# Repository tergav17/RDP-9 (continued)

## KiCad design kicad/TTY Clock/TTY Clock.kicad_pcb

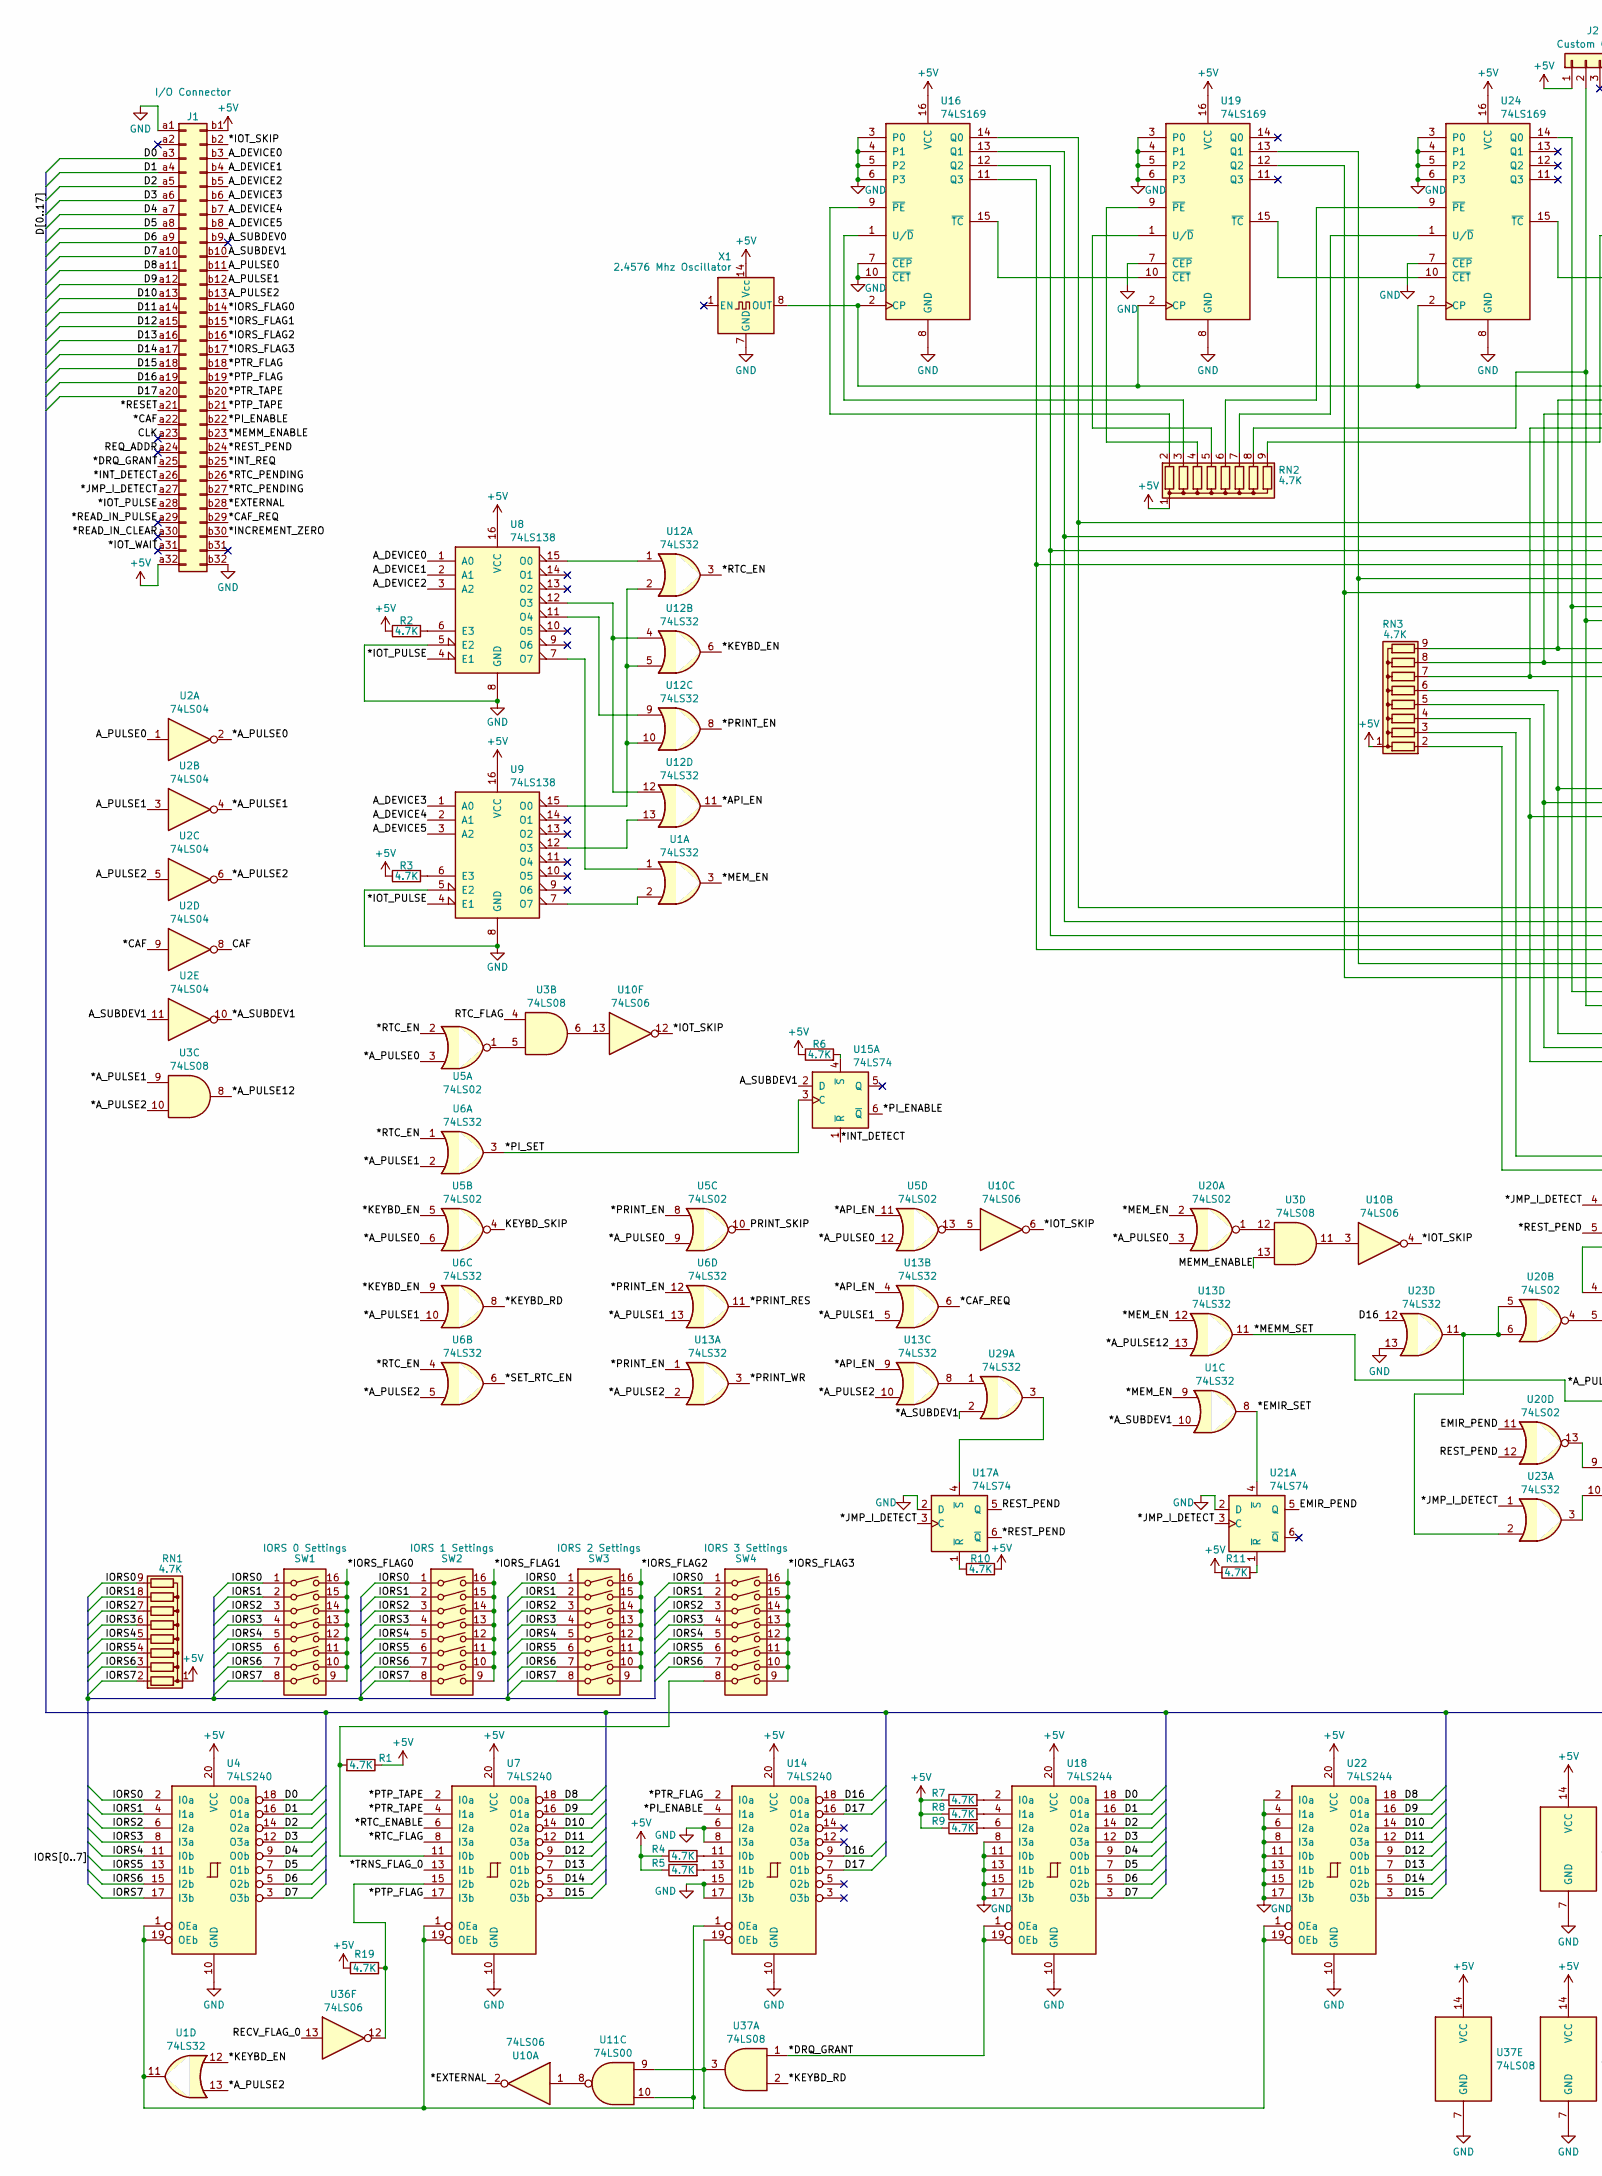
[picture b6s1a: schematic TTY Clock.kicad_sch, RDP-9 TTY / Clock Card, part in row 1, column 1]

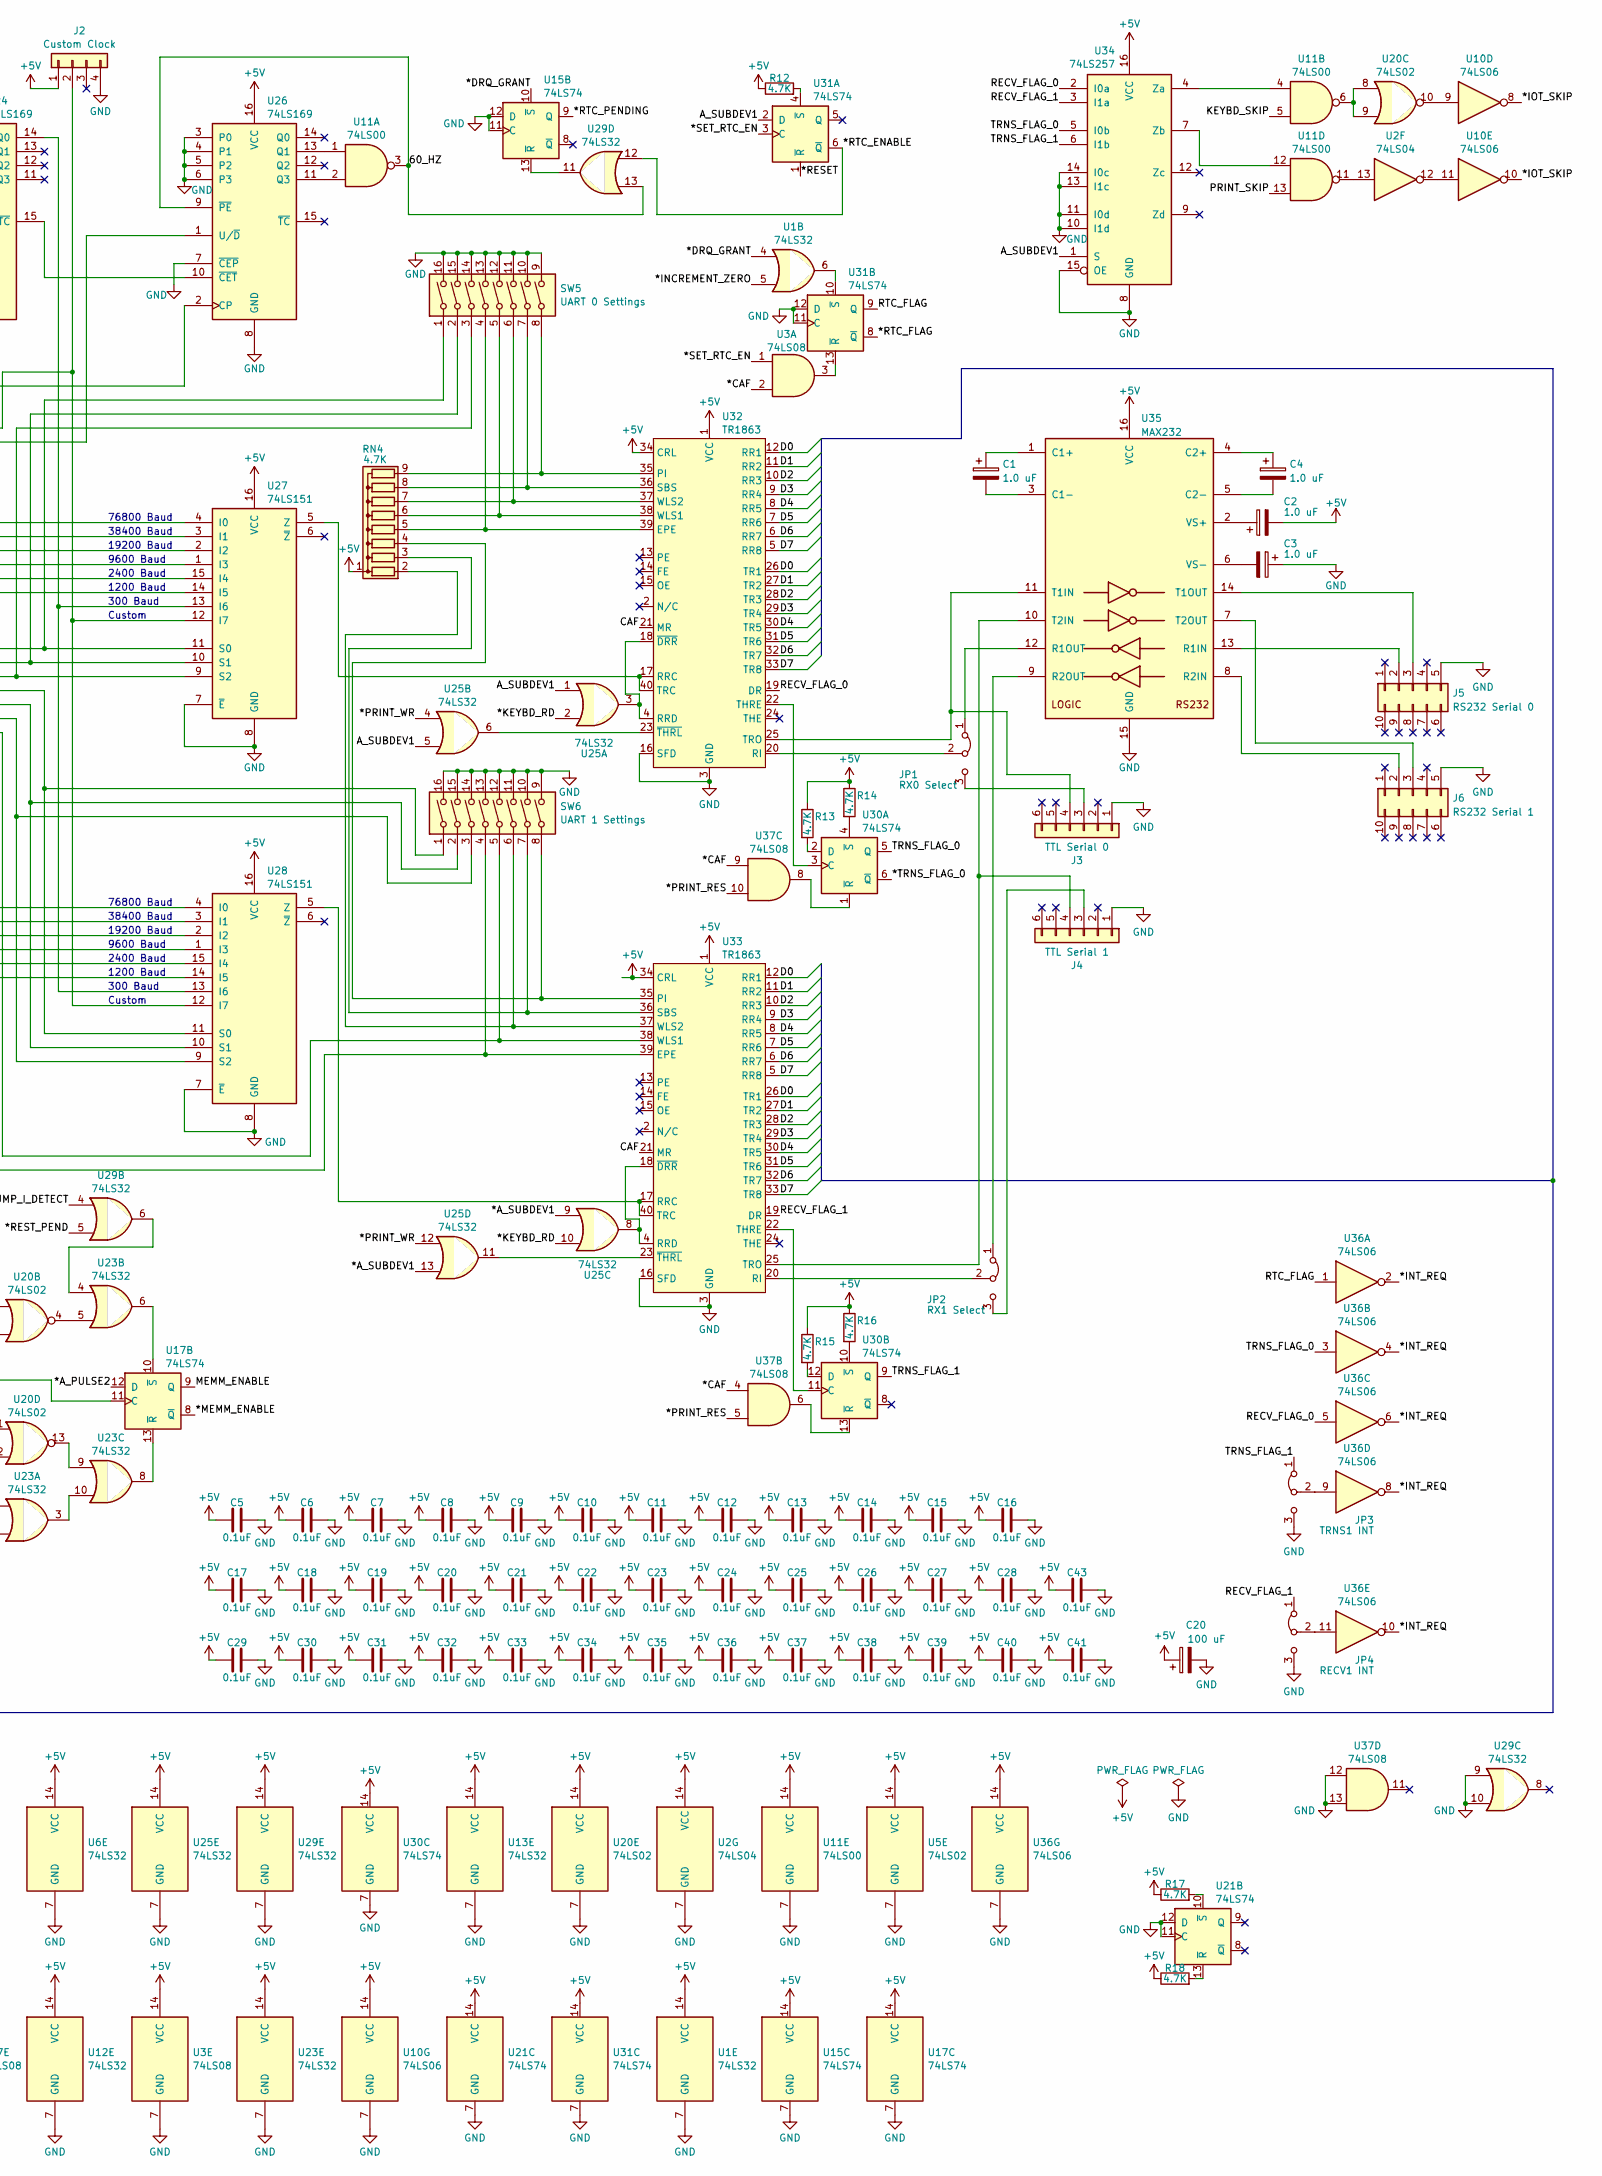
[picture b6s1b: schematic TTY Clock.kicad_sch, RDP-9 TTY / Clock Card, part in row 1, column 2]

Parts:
C1, C2, C3, C4: 1.0 uF; CP_Radial_D5.0mm_P2.00mm
C5, C6, C7, C8, C9, C10, C11, C12, C13, C14, C15, C16, C17, C18, C19, C21, C22, C23, C24, C25, C26, C27, C28, C29, C30, C31, C32, C33, C34, C35, C36, C37, C38, C39, C40, C41, C43: 0.1uF; C_Disc_D5.0mm_W2.5mm_P5.00mm
C20: 100 uF; CP_Radial_D6.3mm_P2.50mm
J1: I/O Connector; DIN41612_B_2x32_Male_Horizontal_THT
J2: Custom Clock; PinHeader_1x04_P2.54mm_Horizontal
J3: TTL Serial 0; PinHeader_1x06_P2.54mm_Horizontal
J4: TTL Serial 1; PinHeader_1x06_P2.54mm_Horizontal
J5: RS232 Serial 0; IDC-Header_2x05_P2.54mm_Horizontal
J6: RS232 Serial 1; IDC-Header_2x05_P2.54mm_Horizontal
JP1: RX0 Select; PinHeader_1x03_P2.54mm_Vertical
JP2: RX1 Select; PinHeader_1x03_P2.54mm_Vertical
JP3: TRNS1 INT; PinHeader_1x03_P2.54mm_Vertical
JP4: RECV1 INT; PinHeader_1x03_P2.54mm_Vertical
R1, R2, R3, R4, R5, R6, R7, R8, R9, R10, R11, R12, R13, R14, R15, R16, R17, R18, R19: 4.7K; R_Axial_DIN0207_L6.3mm_D2.5mm_P7.62mm_Horizontal
RN1, RN2, RN3, RN4: 4.7K; R_Array_SIP9
SW1: IORS 0 Settings; SW_DIP_SPSTx08_Slide_9.78x22.5mm_W7.62mm_P2.54mm
SW2: IORS 1 Settings; SW_DIP_SPSTx08_Slide_9.78x22.5mm_W7.62mm_P2.54mm
SW3: IORS 2 Settings; SW_DIP_SPSTx08_Slide_9.78x22.5mm_W7.62mm_P2.54mm
SW4: IORS 3 Settings; SW_DIP_SPSTx08_Slide_9.78x22.5mm_W7.62mm_P2.54mm
SW5: UART 0 Settings; SW_DIP_SPSTx08_Slide_9.78x22.5mm_W7.62mm_P2.54mm
SW6: UART 1 Settings; SW_DIP_SPSTx08_Slide_9.78x22.5mm_W7.62mm_P2.54mm
U1, U6, U12, U13, U23, U25, U29: 74LS32; DIP-14_W7.62mm
U2: 74LS04; DIP-14_W7.62mm
U3, U37: 74LS08; DIP-14_W7.62mm
U4, U7, U14: 74LS240; DIP-20_W7.62mm
U5, U20: 74LS02; DIP-14_W7.62mm
U8, U9: 74LS138; DIP-16_W7.62mm
U10, U36: 74LS06; DIP-14_W7.62mm
U11: 74LS00; DIP-14_W7.62mm
U15, U17, U21, U30, U31: 74LS74; DIP-14_W7.62mm
U16, U19, U24, U26: 74LS169; DIP-16_W7.62mm
U18, U22: 74LS244; DIP-20_W7.62mm
U27, U28: 74LS151; DIP-16_W7.62mm
U32, U33: TR1863; DIP-40_W15.24mm
U34: 74LS257; DIP-16_W7.62mm
U35: MAX232; DIP-16_W7.62mm
X1: 2.4576 Mhz Oscillator; Oscillator_DIP-14

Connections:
+5V: C2.2, C5.1, C6.1, C7.1, C8.1, C9.1, C10.1, C11.1, C12.1, C13.1, C14.1, C15.1, C16.1, C17.1, C18.1, C19.1, C20.1, C21.1, C22.1, C23.1, C24.1, C25.1, C26.1, C27.1, C28.1, C29.1, C30.1, C31.1, C32.1, C33.1, C34.1, C35.1, C36.1, C37.1, C38.1, C39.1, C40.1, C41.1, C43.1, J1.a32, J1.b1, J2.1, R1.1, R2.1, R3.1, R4.1, R5.1, R6.1, R7.1, R8.1, R9.1, R10.2, R11.1, R12.1, R13.1, R14.1, R15.1, R16.1, R17.1, R18.1, R19.1, RN1.1 (common), RN2.1 (common), RN3.1 (common), RN4.1 (common), U1.14 (VCC), U2.14 (VCC), U3.14 (VCC), U4.20 (VCC), U5.14 (VCC), U6.14 (VCC), U7.20 (VCC), U8.16 (VCC), U9.16 (VCC), U10.14 (VCC), U11.14 (VCC), U12.14 (VCC), U13.14 (VCC), U14.20 (VCC), U15.14 (VCC), U16.16 (VCC), U17.14 (VCC), U18.20 (VCC), U19.16 (VCC), U20.14 (VCC), U21.14 (VCC), U22.20 (VCC), U23.14 (VCC), U24.16 (VCC), U25.14 (VCC), U26.16 (VCC), U27.16 (VCC), U28.16 (VCC), U29.14 (VCC), U30.14 (VCC), U31.14 (VCC), U32.1 (VCC), U32.34 (CRL), U33.1 (VCC), U33.34 (CRL), U34.16 (VCC), U35.16 (VCC), U36.14 (VCC), U37.14 (VCC), X1.14 (Vcc); also elsewhere on the board
/60_HZ: U11.3, U26.9 (~PE), U29.13
/*API_EN: U5.11, U12.11, U13.4, U13.9
/*A_PULSE0: U2.2, U5.3, U5.6, U5.9, U5.12, U20.3
/*A_PULSE1: U2.4, U3.9, U6.2, U6.10, U6.13, U13.5
/*A_PULSE2: U1.13, U2.6, U3.10, U6.5, U13.2, U13.10, U17.12 (D)
/*A_PULSE12: U3.8, U13.13
/*A_SUBDEV1: U1.10, U2.10, U25.9, U25.13, U29.2
/*CAF: J1.a22, U2.9, U3.2, U37.4, U37.9
/*CAF_REQ: J1.b29, U13.6
/*DRQ_GRANT: J1.a25, U1.4, U15.10 (~S), U18.1 (OEa), U18.19 (OEb), U37.1
/*EMIR_SET: U1.8, U21.4 (~S)
/*EXTERNAL: J1.b28, U10.2
/*INCREMENT_ZERO: J1.b30, U1.5
/*INT_DETECT: J1.a26, U15.1 (~R)
/*INT_REQ: J1.b25, U36.2, U36.4, U36.6, U36.8, U36.10
/*IORS_FLAG0: J1.b14, SW1.9, SW1.10, SW1.11, SW1.12, SW1.13, SW1.14, SW1.15, SW1.16
/*IORS_FLAG1: J1.b15, SW2.9, SW2.10, SW2.11, SW2.12, SW2.13, SW2.14, SW2.15, SW2.16
/*IORS_FLAG2: J1.b16, SW3.9, SW3.10, SW3.11, SW3.12, SW3.13, SW3.14, SW3.15, SW3.16
/*IORS_FLAG3: J1.b17, SW4.9, SW4.10, SW4.11, SW4.12, SW4.13, SW4.14, SW4.15, SW4.16
/*IOT_PULSE: J1.a28, U8.4 (E1), U9.4 (E1)
/*IOT_SKIP: J1.b2, U10.4, U10.6, U10.8, U10.10, U10.12
/*IOT_WAIT: J1.a31
/*JMP_I_DETECT: J1.a27, U17.3 (C), U21.3 (C), U23.1, U29.4
/*KEYBD_EN: U1.12, U5.5, U6.9, U12.6
/*KEYBD_RD: U6.8, U25.2, U25.10, U37.2
/*MEMM_ENABLE: J1.b23, U17.8 (~Q)
/*MEMM_SET: U13.11, U17.11 (C)
/*MEM_EN: U1.3, U1.9, U13.12, U20.2
/*PI_ENABLE: J1.b22, U14.4 (I1a), U15.6 (~Q)
/*PI_SET: U6.3, U15.3 (C)
/*PRINT_EN: U5.8, U6.12, U12.8, U13.1
/*PRINT_RES: U6.11, U37.5, U37.10
/*PRINT_WR: U13.3, U25.4, U25.12
/*PTP_FLAG: J1.b19, U7.17 (I3b)
/*PTP_TAPE: J1.b21, U7.2 (I0a)
/*PTR_FLAG: J1.b18, U14.2 (I0a)
/*PTR_TAPE: J1.b20, U7.4 (I1a)
/*READ_IN_CLEAR: J1.a30
/*READ_IN_PULSE: J1.a29
/*RESET: J1.a21, U31.1 (~R)
/*REST_PEND: J1.b24, U17.6 (~Q), U29.5
/*RTC_EN: U5.2, U6.1, U6.4, U12.3
/*RTC_ENABLE: U7.6 (I2a), U29.12, U31.6 (~Q)
/*RTC_FLAG: U7.8 (I3a), U31.8 (~Q)
/*RTC_PENDING: J1.b26, J1.b27, U15.9 (Q)
/*SET_RTC_EN: U3.1, U6.6, U31.3 (C)
/*TRNS_FLAG_0: U7.13 (I1b), U30.6 (~Q)
/A_DEVICE0: J1.b3, U8.1 (A0)
/A_DEVICE1: J1.b4, U8.2 (A1)
/A_DEVICE2: J1.b5, U8.3 (A2)
/A_DEVICE3: J1.b6, U9.1 (A0)
/A_DEVICE4: J1.b7, U9.2 (A1)
/A_DEVICE5: J1.b8, U9.3 (A2)
/A_PULSE0: J1.b11, U2.1
/A_PULSE1: J1.b12, U2.3
/A_PULSE2: J1.b13, U2.5
/A_SUBDEV0: J1.b9
/A_SUBDEV1: J1.b10, U2.11, U15.2 (D), U25.1, U25.5, U31.2 (D), U34.1 (S)
/CAF: U2.8, U32.21 (MR), U33.21 (MR)
/CLK: J1.a23
/D0: J1.a3, U4.18 (O0a), U18.18 (O0a), U32.12 (RR1), U32.26 (TR1), U33.12 (RR1), U33.26 (TR1)
/D1: J1.a4, U4.16 (O1a), U18.16 (O1a), U32.11 (RR2), U32.27 (TR2), U33.11 (RR2), U33.27 (TR2)
/D2: J1.a5, U4.14 (O2a), U18.14 (O2a), U32.10 (RR3), U32.28 (TR3), U33.10 (RR3), U33.28 (TR3)
/D3: J1.a6, U4.12 (O3a), U18.12 (O3a), U32.9 (RR4), U32.29 (TR4), U33.9 (RR4), U33.29 (TR4)
/D4: J1.a7, U4.9 (O0b), U18.9 (O0b), U32.8 (RR5), U32.30 (TR5), U33.8 (RR5), U33.30 (TR5)
/D5: J1.a8, U4.7 (O1b), U18.7 (O1b), U32.7 (RR6), U32.31 (TR6), U33.7 (RR6), U33.31 (TR6)
/D6: J1.a9, U4.5 (O2b), U18.5 (O2b), U32.6 (RR7), U32.32 (TR7), U33.6 (RR7), U33.32 (TR7)
/D7: J1.a10, U4.3 (O3b), U18.3 (O3b), U32.5 (RR8), U32.33 (TR8), U33.5 (RR8), U33.33 (TR8)
/D8: J1.a11, U7.18 (O0a), U22.18 (O0a)
/D9: J1.a12, U7.16 (O1a), U22.16 (O1a)
/D10: J1.a13, U7.14 (O2a), U22.14 (O2a)
/D11: J1.a14, U7.12 (O3a), U22.12 (O3a)
/D12: J1.a15, U7.9 (O0b), U22.9 (O0b)
/D13: J1.a16, U7.7 (O1b), U22.7 (O1b)
/D14: J1.a17, U7.5 (O2b), U22.5 (O2b)
/D15: J1.a18, U7.3 (O3b), U22.3 (O3b)
/D16: J1.a19, U14.9 (O0b), U14.18 (O0a), U23.12
/D17: J1.a20, U14.7 (O1b), U14.16 (O1a)
/EMIR_PEND: U20.11, U21.5 (Q)
/IORS0: RN1.9 (R8), SW1.1, SW2.1, SW3.1, SW4.1, U4.2 (I0a)
/IORS1: RN1.8 (R7), SW1.2, SW2.2, SW3.2, SW4.2, U4.4 (I1a)
/IORS2: RN1.7 (R6), SW1.3, SW2.3, SW3.3, SW4.3, U4.6 (I2a)
/IORS3: RN1.6 (R5), SW1.4, SW2.4, SW3.4, SW4.4, U4.8 (I3a)
/IORS4: RN1.5 (R4), SW1.5, SW2.5, SW3.5, SW4.5, U4.11 (I0b)
/IORS5: RN1.4 (R3), SW1.6, SW2.6, SW3.6, SW4.6, U4.13 (I1b)
/IORS6: RN1.3 (R2), SW1.7, SW2.7, SW3.7, SW4.7, U4.15 (I2b)
/IORS7: RN1.2 (R1), SW1.8, SW2.8, SW3.8, U4.17 (I3b)
/KEYBD_SKIP: U5.4, U11.5
/MEMM_ENABLE: U3.13, U17.9 (Q)
/PRINT_SKIP: U5.10, U11.13
/RECV_FLAG_0: U32.19 (DR), U34.2 (I0a), U36.5, U36.13
/RECV_FLAG_1: JP4.1 (A), U33.19 (DR), U34.3 (I1a)
/REQ_ADDR: J1.a24
/REST_PEND: U17.5 (Q), U20.12
/RTC_FLAG: U3.4, U31.9 (Q), U36.1
/TRNS_FLAG_0: U30.5 (Q), U34.5 (I0b), U36.3
/TRNS_FLAG_1: JP3.1 (A), U30.9 (Q), U34.6 (I1b)
GND: C3.1, C5.2, C6.2, C7.2, C8.2, C9.2, C10.2, C11.2, C12.2, C13.2, C14.2, C15.2, C16.2, C17.2, C18.2, C19.2, C20.2, C21.2, C22.2, C23.2, C24.2, C25.2, C26.2, C27.2, C28.2, C29.2, C30.2, C31.2, C32.2, C33.2, C34.2, C35.2, C36.2, C37.2, C38.2, C39.2, C40.2, C41.2, C43.2, J1.a1, J1.b32, J2.4, J3.1, J4.1, J5.5, J6.5, JP3.3 (B), JP4.3 (B), SW5.9, SW5.10, SW5.11, SW5.12, SW5.13, SW5.14, SW5.15, SW5.16, SW6.9, SW6.10, SW6.11, SW6.12, SW6.13, SW6.14, SW6.15, SW6.16, U1.7 (GND), U2.7 (GND), U3.7 (GND), U4.10 (GND), U5.7 (GND), U6.7 (GND), U7.10 (GND), U8.5 (E2), U8.8 (GND), U9.5 (E2), U9.8 (GND), U10.7 (GND), U11.7 (GND), U12.7 (GND), U13.7 (GND), U14.6 (I2a), U14.8 (I3a), U14.10 (GND), U14.15 (I2b), U14.17 (I3b), U15.7 (GND), U15.11 (C), U15.12 (D), U16.3 (P0), U16.4 (P1), U16.5 (P2), U16.6 (P3), U16.7 (~CEP), U16.8 (GND), U16.10 (~CET), U17.2 (D), U17.7 (GND), U18.8 (I3a), U18.10 (GND), U18.11 (I0b), U18.13 (I1b), U18.15 (I2b), U18.17 (I3b), U19.3 (P0), U19.4 (P1), U19.5 (P2), U19.6 (P3), U19.7 (~CEP), U19.8 (GND), U20.7 (GND), U21.2 (D), U21.7 (GND), U21.11 (C), U21.12 (D), U22.2 (I0a), U22.4 (I1a), U22.6 (I2a), U22.8 (I3a), U22.10 (GND), U22.11 (I0b), U22.13 (I1b), U22.15 (I2b), U22.17 (I3b), U23.7 (GND), U23.13, U24.3 (P0), U24.4 (P1), U24.5 (P2), U24.6 (P3), U24.7 (~CEP), U24.8 (GND), U25.7 (GND), U26.3 (P0), U26.4 (P1), U26.5 (P2), U26.6 (P3), U26.7 (~CEP), U26.8 (GND), U27.7 (~E), U27.8 (GND), U28.7 (~E), U28.8 (GND), U29.7 (GND), U29.9, U29.10, U30.7 (GND), U31.7 (GND), U31.11 (C), U31.12 (D), U32.3 (GND), U32.16 (SFD), U33.3 (GND), U33.16 (SFD), U34.8 (GND), U34.10 (I1d), U34.11 (I0d), U34.13 (I1c), U34.14 (I0c), U34.15 (OE), U35.15 (GND), U36.7 (GND), U37.7 (GND), U37.12, U37.13, X1.7 (GND); also elsewhere on the board
unnamed: J2.2, RN2.8 (R7), U27.12 (I7), U28.12 (I7)
unnamed: J3.3, JP1.3 (B)
unnamed: J3.4, U32.25 (TRO), U35.11 (T1IN)
unnamed: J4.3, JP2.3 (B)
unnamed: J4.4, U33.25 (TRO), U35.10 (T2IN)
unnamed: J5.2, U35.13 (R1IN)
unnamed: J5.3, U35.14 (T1OUT)
unnamed: J6.2, U35.8 (R2IN)
unnamed: J6.3, U35.7 (T2OUT)
unnamed: JP1.1 (A), U35.12 (R1OUT)
unnamed: JP1.2 (C), U32.20 (RI)
unnamed: JP2.1 (A), U35.9 (R2OUT)
unnamed: JP2.2 (C), U33.20 (RI)
unnamed: JP3.2 (C), U36.9
unnamed: JP4.2 (C), U36.11
unnamed: RN2.2 (R1), U16.9 (~PE)
unnamed: RN2.3 (R2), U16.1 (U/~D)
unnamed: RN2.4 (R3), U19.9 (~PE)
unnamed: RN2.5 (R4), U19.1 (U/~D)
unnamed: RN2.6 (R5), U24.9 (~PE)
unnamed: RN2.7 (R6), U24.1 (U/~D)
unnamed: RN2.9 (R8), U26.1 (U/~D)
unnamed: RN3.2 (R1), SW6.4, U33.39 (EPE)
unnamed: RN3.3 (R2), SW6.5, U33.38 (WLS1)
unnamed: RN3.4 (R3), SW6.3, U28.9 (S2)
unnamed: RN3.5 (R4), SW6.2, U28.10 (S1)
unnamed: RN3.6 (R5), SW6.1, U28.11 (S0)
unnamed: RN3.7 (R6), SW5.3, U27.9 (S2)
unnamed: RN3.8 (R7), SW5.2, U27.10 (S1)
unnamed: RN3.9 (R8), SW5.1, U27.11 (S0)
unnamed: RN4.2 (R1), SW6.6, U33.37 (WLS2)
unnamed: RN4.3 (R2), SW6.7, U33.36 (SBS)
unnamed: RN4.4 (R3), SW6.8, U33.35 (PI)
unnamed: RN4.5 (R4), SW5.4, U32.39 (EPE)
unnamed: RN4.6 (R5), SW5.5, U32.38 (WLS1)
unnamed: RN4.7 (R6), SW5.6, U32.37 (WLS2)
unnamed: RN4.8 (R7), SW5.7, U32.36 (SBS)
unnamed: RN4.9 (R8), SW5.8, U32.35 (PI)
unnamed: U3.5, U5.1
unnamed: R1.2, SW4.8, U7.11 (I0b)
unnamed: R19.2, U7.15 (I2b), U36.12
unnamed: R2.2, U8.6 (E3)
unnamed: U8.15 (O0), U12.1
unnamed: U8.12 (O3), U12.4, U12.12
unnamed: U8.11 (O4), U12.9
unnamed: U1.1, U8.7 (O7)
unnamed: R3.2, U9.6 (E3)
unnamed: U9.15 (O0), U12.2, U12.5, U12.10
unnamed: U9.12 (O3), U12.13
unnamed: U1.2, U9.7 (O7)
unnamed: U10.1, U11.8
unnamed: U3.11, U10.3
unnamed: U5.13, U10.5
unnamed: U10.9, U20.10
unnamed: U2.12, U10.11
unnamed: U3.6, U10.13
unnamed: U11.6, U20.8, U20.9
unnamed: U2.13, U11.11
unnamed: U13.8, U29.1
unnamed: R4.2, U14.11 (I0b)
unnamed: R5.2, U14.13 (I1b)
unnamed: U1.11, U4.1 (OEa), U4.19 (OEb), U7.1 (OEa), U7.19 (OEb), U11.10, U14.1 (OEa)
unnamed: U11.9, U14.19 (OEb), U22.1 (OEa), U22.19 (OEb), U37.3
unnamed: R6.2, U15.4 (~S)
unnamed: U15.13 (~R), U29.11
unnamed: U16.2 (CP), U19.2 (CP), U24.2 (CP), U26.2 (CP), X1.8 (OUT)
unnamed: U16.14 (Q0), U27.4 (I0), U28.4 (I0)
unnamed: U16.13 (Q1), U27.3 (I1), U28.3 (I1)
unnamed: U16.12 (Q2), U27.2 (I2), U28.2 (I2)
unnamed: U16.11 (Q3), U27.1 (I3), U28.1 (I3)
unnamed: U16.15 (~TC), U19.10 (~CET)
unnamed: R10.1, U17.1 (~R)
unnamed: U17.4 (~S), U29.3
unnamed: U17.13 (~R), U23.8
unnamed: U17.10 (~S), U23.6
unnamed: R7.2, U18.2 (I0a)
unnamed: R8.2, U18.4 (I1a)
unnamed: R9.2, U18.6 (I2a)
unnamed: U19.13 (Q1), U27.15 (I4), U28.15 (I4)
unnamed: U19.12 (Q2), U27.14 (I5), U28.14 (I5)
unnamed: U19.15 (~TC), U24.10 (~CET)
unnamed: U3.12, U20.1
unnamed: U20.4, U23.5
unnamed: U20.5, U20.6, U23.2, U23.11
unnamed: U20.13, U23.9
unnamed: R11.2, U21.1 (~R)
unnamed: R18.2, U21.13 (~R)
unnamed: R17.2, U21.10 (~S)
unnamed: U23.4, U29.6
unnamed: U23.3, U23.10
unnamed: U24.14 (Q0), U27.13 (I6), U28.13 (I6)
unnamed: U24.15 (~TC), U26.10 (~CET)
unnamed: U11.1, U26.13 (Q1)
unnamed: U11.2, U26.11 (Q3)
unnamed: U27.5 (Z), U32.17 (RRC), U32.40 (TRC)
unnamed: U28.5 (Z), U33.17 (RRC), U33.40 (TRC)
unnamed: U30.3 (C), U32.22 (THRE)
unnamed: R13.2, U30.2 (D)
unnamed: U30.1 (~R), U37.8
unnamed: R14.2, U30.4 (~S)
unnamed: U30.11 (C), U33.22 (THRE)
unnamed: R15.2, U30.12 (D)
unnamed: U30.13 (~R), U37.6
unnamed: R16.2, U30.10 (~S)
unnamed: R12.2, U31.4 (~S)
unnamed: U3.3, U31.13 (~R)
unnamed: U1.6, U31.10 (~S)
unnamed: U25.3, U32.4 (RRD), U32.18 (~DRR)
unnamed: U25.6, U32.23 (~THRL)
unnamed: U25.8, U33.4 (RRD), U33.18 (~DRR)
unnamed: U25.11, U33.23 (~THRL)
unnamed: U11.4, U34.4 (Za)
unnamed: U11.12, U34.7 (Zb)
unnamed: C1.1, U35.1 (C1+)
unnamed: C1.2, U35.3 (C1-)
unnamed: C4.1, U35.4 (C2+)
unnamed: C4.2, U35.5 (C2-)
unnamed: C2.1, U35.2 (VS+)
unnamed: C3.2, U35.6 (VS-)

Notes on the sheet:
19200 Baud
1200 Baud
9600 Baud
Custom
300 Baud
76800 Baud
2400 Baud
38400 Baud

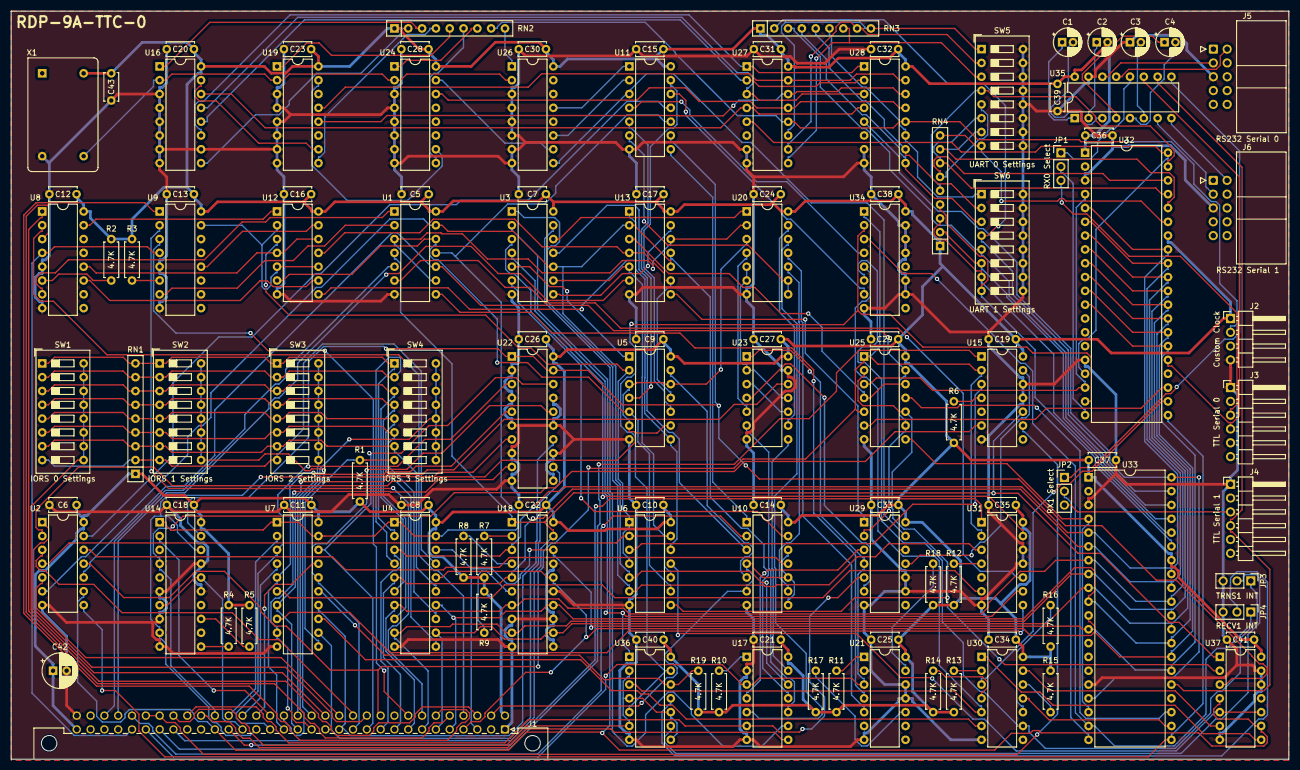
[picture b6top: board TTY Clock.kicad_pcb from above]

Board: 2 copper layers, 234.9 x 137.5 mm, 120 parts (0 on the bottom side), 212 nets.

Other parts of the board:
C42: 100 uF; CP_Radial_D6.3mm_P2.50mm

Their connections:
+5V: C42.1; also elsewhere on the board
GND: C42.2; also elsewhere on the board
